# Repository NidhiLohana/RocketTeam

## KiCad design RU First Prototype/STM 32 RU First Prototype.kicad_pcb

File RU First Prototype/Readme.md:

This is the first prototype of RU

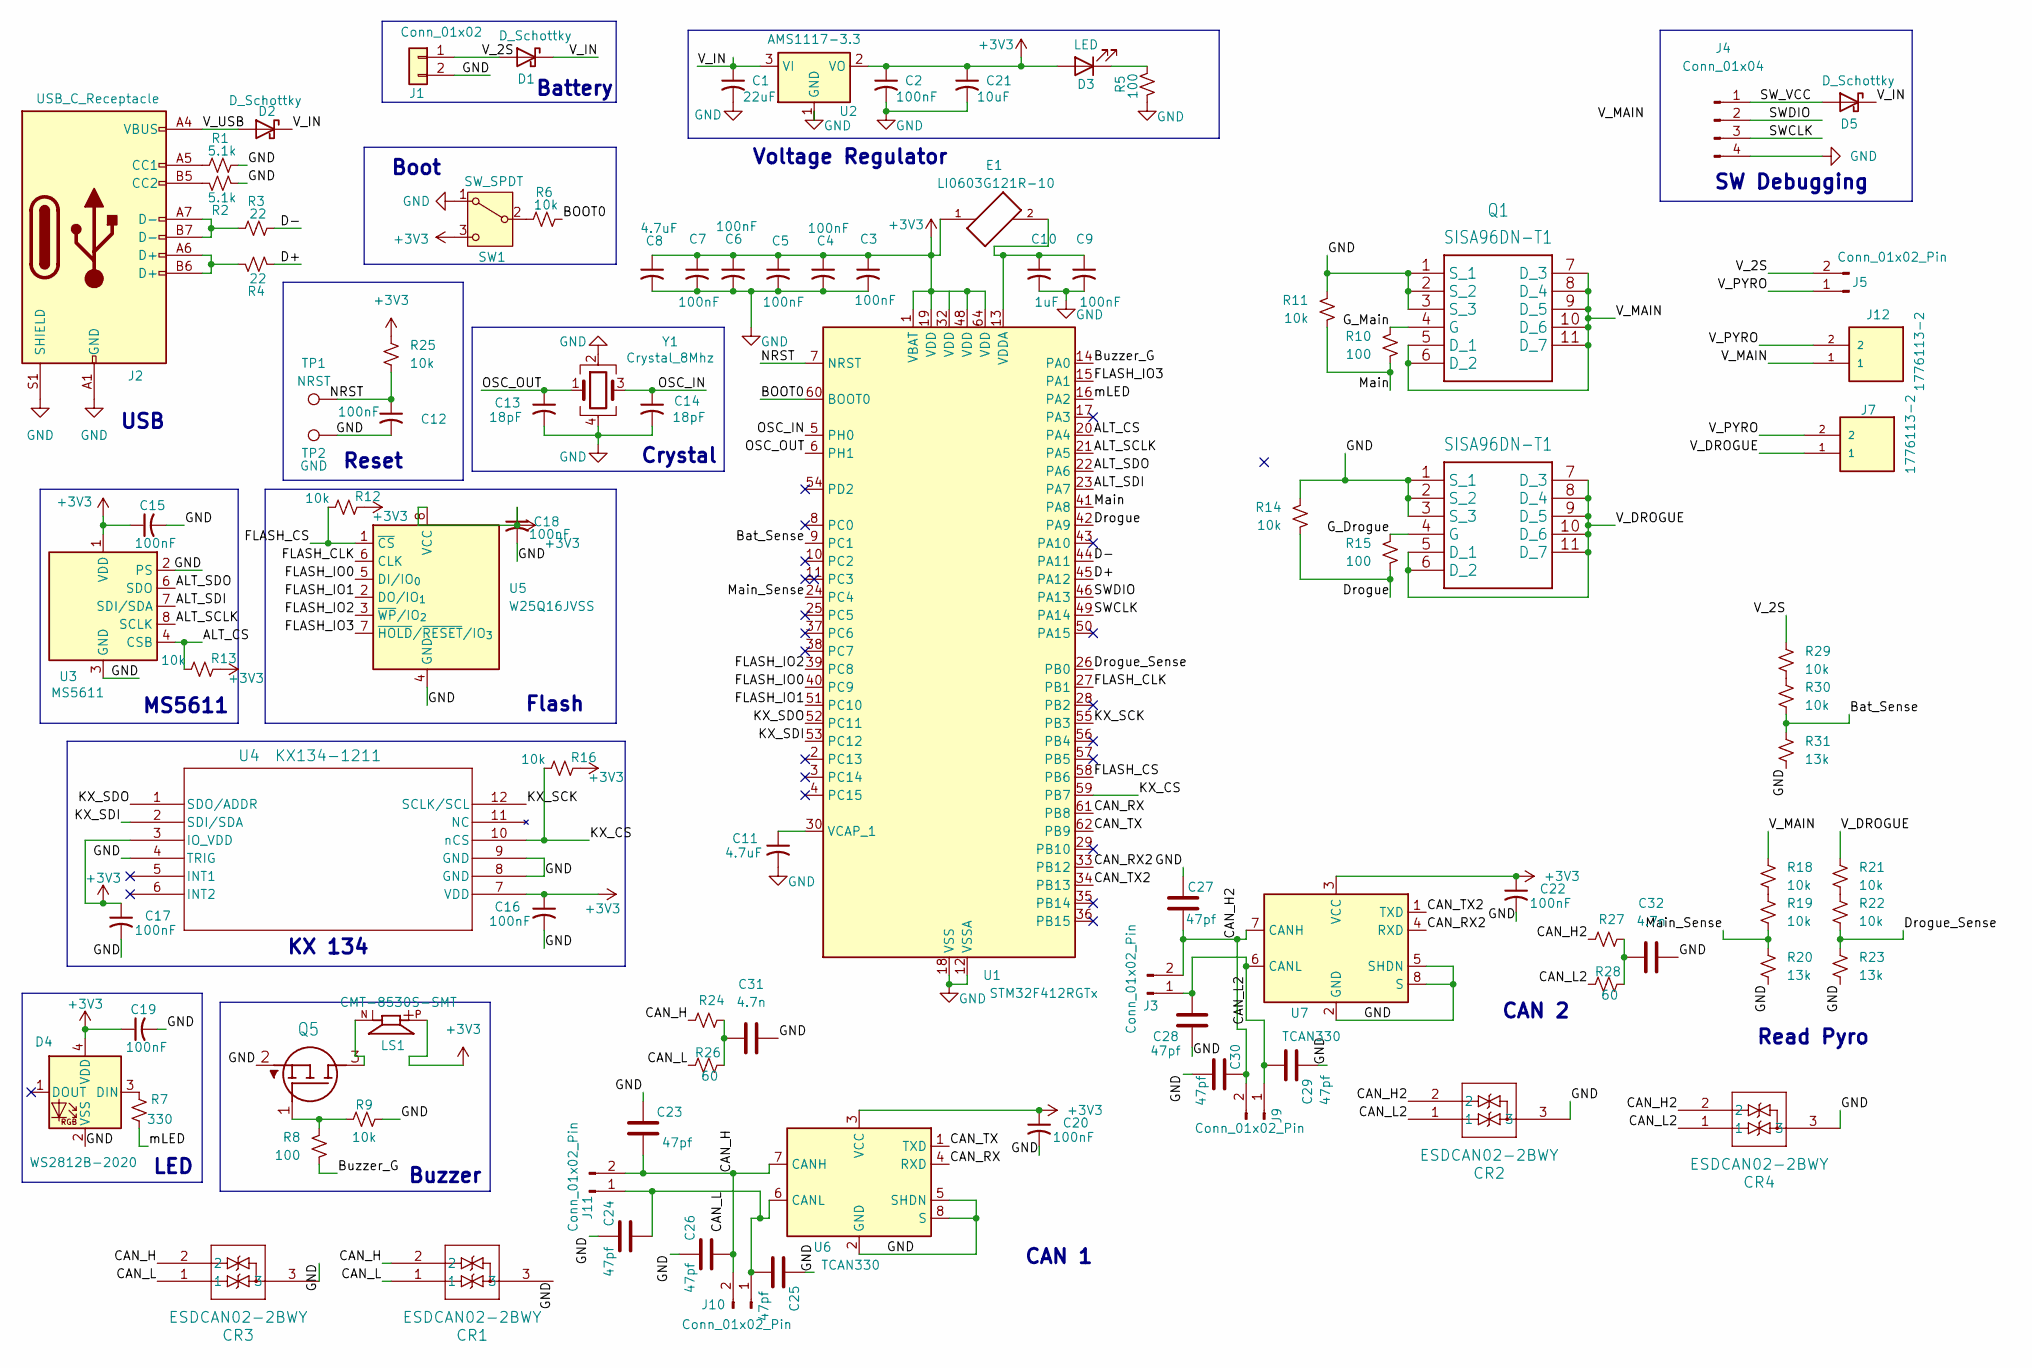
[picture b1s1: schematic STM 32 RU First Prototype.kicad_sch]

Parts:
C1: 22uF; C_0603_1608Metric
C2, C3, C4, C5, C6, C7, C9, C12, C15, C16, C17, C18, C19, C20, C22: 100nF; C_0603_1608Metric
C8, C11: 4.7uF; C_0603_1608Metric
C10: 1uF; C_0603_1608Metric
C13, C14: 18pF; C_0603_1608Metric
C21: 10uF; C_0603_1608Metric
C23, C24, C25, C26, C27, C28, C29, C30: 47pf; C_0603_1608Metric
C31, C32: 4.7n; C_0603_1608Metric
CR1, CR2, CR3, CR4: ESDCAN02-2BWY; SOT323-3L_STM
D1, D2, D5: D_Schottky; D_SOD-128
D3: LED; D_0603_1608Metric
D4: WS2812B-2020; LED_WS2812B-2020_PLCC4_2.0x2.0mm
E1: LI0603G121R-10; FB_LI0603G121R-10; PARTREV C
J1: Conn_01x02; AMASS_XT30U-M_1x02_P5.0mm_Vertical
J2: USB_C_Receptacle; USB_C_Receptacle_GCT_USB4105-xx-A_16P_TopMnt_Horizontal
J3, J9, J10, J11: Conn_01x02_Pin; JST_EH_B2B-EH-A_1x02_P2.50mm_Vertical
J4: Conn_01x04; PinHeader_1x04_P2.54mm_Vertical
J5: Conn_01x02_Pin; AMASS_XT30U-M_1x02_P5.0mm_Vertical
J7, J12: 1776113-2; TE_1776113-2; PART_REV P
LS1: CMT-8530S-SMT; CUI_CMT-8530S-SMT
Q1, Q3: SISA96DN-T1; SIS862DNT1GE3
Q5: SOT95P240X115-3N
R1, R2: 5.1k; R_0603_1608Metric
R3, R4: 22; R_0603_1608Metric
R5, R8, R10, R15: 100; R_0603_1608Metric
R6, R9, R11, R12, R13, R14, R16, R18, R19, R21, R22, R25, R29, R30: 10k; R_0603_1608Metric
R7: 330; R_0603_1608Metric
R20, R23, R31: 13k; R_0603_1608Metric
R24, R26, R27, R28: 60; R_0603_1608Metric
SW1: SW_SPDT; SW_SPDT_PCM12
TP1: NRST; TestPoint_Pad_2.0x2.0mm
TP2: GND; TestPoint_Pad_2.0x2.0mm
U1: STM32F412RGTx; LQFP-64_10x10mm_P0.5mm
U2: AMS1117-3.3; SOT-223-3_TabPin2
U3: MS5611; LGA-8_3x5mm_P1.25mm
U4: KX134-1211; XDCR_KX003-1077
U5: W25Q16JVSS; SOIC-8_5.3x5.3mm_P1.27mm
U6, U7: TCAN330; SOIC-8_3.9x4.9mm_P1.27mm
Y1: Crystal_8Mhz; Crystal_SMD_7050-4Pin_7.0x5.0mm

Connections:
+3V3: C2.1, C3.1, C4.1, C5.1, C6.1, C7.1, C8.1, C15.1, C16.1, C17.1, C18.1, C19.1, C20.1, C21.1, C22.1, D3.2 (A), D4.4 (VDD), E1.1, LS1.P, R12.2, R13.2, R16.2, R25.1, SW1.3 (C), U1.1 (VBAT), U1.19 (VDD), U1.32 (VDD), U1.48 (VDD), U1.64 (VDD), U2.2 (VO), U3.1 (VDD), U4.3 (IO_VDD), U4.7 (VDD), U5.8 (VCC), U6.3 (VCC), U7.3 (VCC)
/ALT_CS: R13.1, U1.20 (PA4), U3.4 (CSB), U3.5 (CSB)
/ALT_SCLK: U1.21 (PA5), U3.8 (SCLK)
/ALT_SDI: U1.23 (PA7), U3.7 (SDI/SDA)
/ALT_SDO: U1.22 (PA6), U3.6 (SDO)
/BOOT0: R6.2, U1.60 (BOOT0)
/Bat_Sense: R30.2, R31.1, U1.9 (PC1)
/Buzzer_G: R8.2, U1.14 (PA0)
/CAN_H: C23.2, C26.2, CR1.2, CR3.2, J10.2, J11.2, R24.1, U6.7 (CANH)
/CAN_H2: C27.2, C30.2, CR2.2, CR4.2, J3.2, J9.2, R27.1, U7.7 (CANH)
/CAN_L: C24.2, C25.2, CR1.1, CR3.1, J10.1, J11.1, R26.1, U6.6 (CANL)
/CAN_L2: C28.2, C29.2, CR2.1, CR4.1, J3.1, J9.1, R28.1, U7.6 (CANL)
/CAN_RX: U1.61 (PB8), U6.4 (RXD)
/CAN_RX2: U1.33 (PB12), U7.4 (RXD)
/CAN_TX: U1.62 (PB9), U6.1 (TXD)
/CAN_TX2: U1.34 (PB13), U7.1 (TXD)
/D+: R4.2, U1.45 (PA12)
/D-: R3.2, U1.44 (PA11)
/Drogue: R14.2, R15.2, U1.42 (PA9)
/Drogue_Sense: R22.2, R23.1, U1.26 (PB0)
/FLASH_CLK: U1.27 (PB1), U5.6 (CLK)
/FLASH_CS: R12.1, U1.58 (PB6), U5.1 (~CS)
/FLASH_IO0: U1.40 (PC9), U5.5 (DI/IO_{0})
/FLASH_IO1: U1.51 (PC10), U5.2 (DO/IO_{1})
/FLASH_IO2: U1.39 (PC8), U5.3 (~WP/IO_{2})
/FLASH_IO3: U1.15 (PA1), U5.7 (~HOLD/~RESET/IO_{3})
/G_Drogue: Q3.4 (G), R15.1
/G_Main: Q1.4 (G), R10.1
/KX_CS: R16.1, U1.59 (PB7), U4.10 (nCS)
/KX_SCK: U1.55 (PB3), U4.12 (SCLK/SCL)
/KX_SDI: U1.53 (PC12), U4.2 (SDI/SDA)
/KX_SDO: U1.52 (PC11), U4.1 (SDO/ADDR)
/Main: R10.2, R11.2, U1.41 (PA8)
/Main_Sense: R19.2, R20.1, U1.24 (PC4)
/NRST: C12.1, R25.2, TP1.1 (1_1), U1.7 (NRST)
/OSC_IN: C14.1, U1.5 (PH0), Y1.3
/OSC_OUT: C13.1, U1.6 (PH1), Y1.1
/SWCLK: J4.3, U1.49 (PA14)
/SWDIO: J4.2, U1.46 (PA13)
/SW_VCC: D5.2 (A), J4.1
/V_2S: D1.2 (A), J1.1, J5.2, R29.1
/V_DROGUE: J7.1, Q3.5 (D_1), Q3.6 (D_2), Q3.7 (D_3), Q3.8 (D_4), Q3.9 (D_5), Q3.10 (D_6), Q3.11 (D_7), R21.1
/V_IN: C1.1, D1.1 (K), D2.1 (K), D5.1 (K), U2.3 (VI)
/V_MAIN: J12.1, Q1.5 (D_1), Q1.6 (D_2), Q1.7 (D_3), Q1.8 (D_4), Q1.9 (D_5), Q1.10 (D_6), Q1.11 (D_7), R18.1
/V_PYRO: J5.1, J7.2, J12.2
/V_USB: D2.2 (A), J2.A4 (VBUS), J2.A9 (VBUS), J2.B4 (VBUS), J2.B9 (VBUS)
/mLED: R7.2, U1.16 (PA2)
GND: C1.2, C2.2, C3.2, C4.2, C5.2, C6.2, C7.2, C8.2, C9.2, C10.2, C11.2, C12.2, C13.2, C14.2, C15.2, C16.2, C17.2, C18.2, C19.2, C20.2, C21.2, C22.2, C23.1, C24.1, C25.1, C26.1, C27.1, C28.1, C29.1, C30.1, C31.2, C32.2, CR1.3, CR2.3, CR3.3, CR4.3, D4.2 (VSS), J1.2, J2.A1 (GND), J2.A12 (GND), J2.B1 (GND), J2.B12 (GND), J2.S1 (SHIELD), J4.4, Q1.1 (S_1), Q1.2 (S_2), Q1.3 (S_3), Q3.1 (S_1), Q3.2 (S_2), Q3.3 (S_3), Q5.2 (S), R1.2, R2.2, R5.2, R9.1, R11.1, R14.1, R20.2, R23.2, R31.2, SW1.1 (A), TP2.1 (1_1), U1.12 (VSSA), U1.18 (VSS), U1.31 (VSS), U1.47 (VSS), U1.63 (VSS), U2.1 (GND), U3.2 (PS), U3.3 (GND), U4.4 (TRIG), U4.8 (GND), U4.9 (GND), U5.4 (GND), U6.2 (GND), U6.5 (SHDN), U6.8 (S), U7.2 (GND), U7.5 (SHDN), U7.8 (S), Y1.2, Y1.4
unnamed: C31.1, R24.2, R26.2
unnamed: C32.1, R27.2, R28.2
unnamed: D3.1 (K), R5.1
unnamed: D4.3 (DIN), R7.1
unnamed: J2.A5 (CC1), R1.1
unnamed: J2.B5 (CC2), R2.1
unnamed: J2.A6 (D+), J2.B6 (D+), R4.1
unnamed: J2.A7 (D-), J2.B7 (D-), R3.1
unnamed: LS1.N, Q5.3 (D)
unnamed: Q5.1 (G), R8.1, R9.2
unnamed: R18.2, R19.1
unnamed: R21.2, R22.1
unnamed: R29.2, R30.1
unnamed: R6.1, SW1.2 (B)
unnamed: C11.1, U1.30 (VCAP_1)
unnamed: C9.1, C10.1, E1.2, U1.13 (VDDA)

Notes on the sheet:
Flash
Voltage Regulator
Buzzer
LED
Battery
Reset
USB
MS5611
CAN 1
Boot
SW Debugging
CAN 2
KX 134
Read Pyro
Crystal

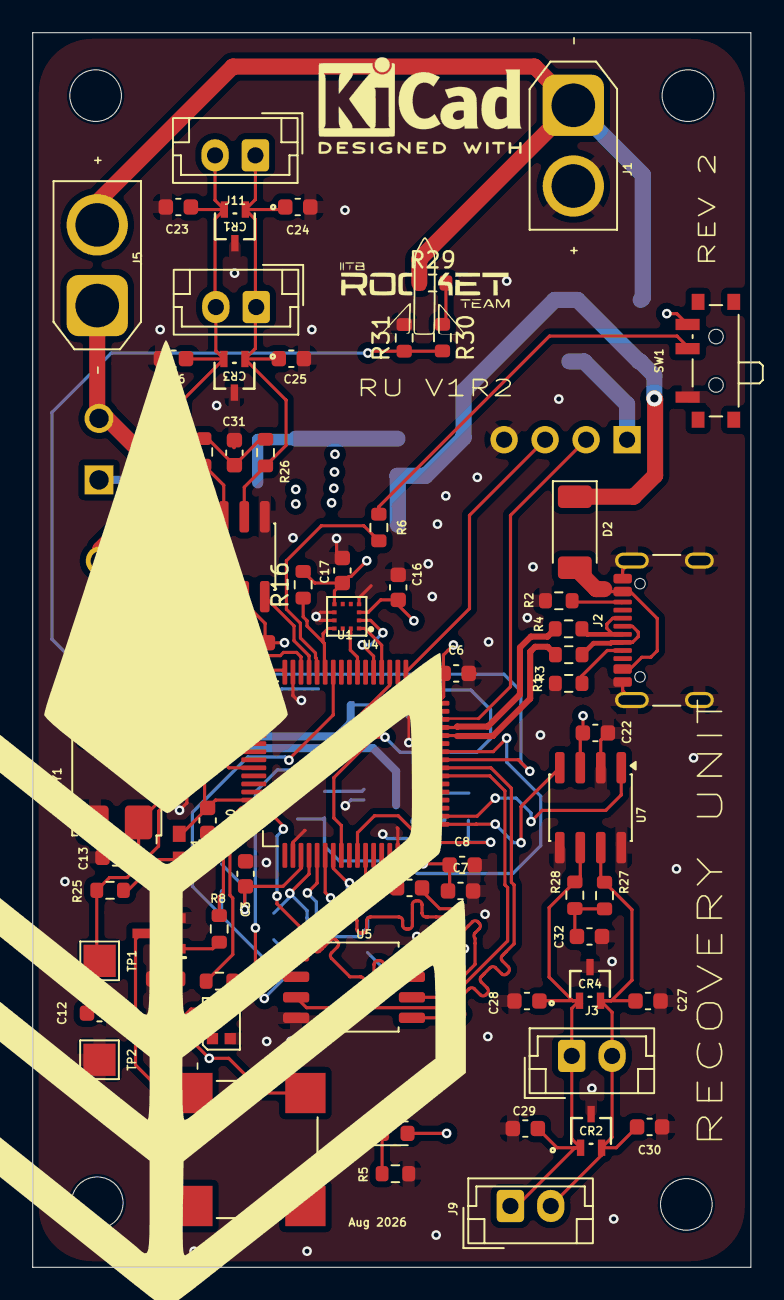
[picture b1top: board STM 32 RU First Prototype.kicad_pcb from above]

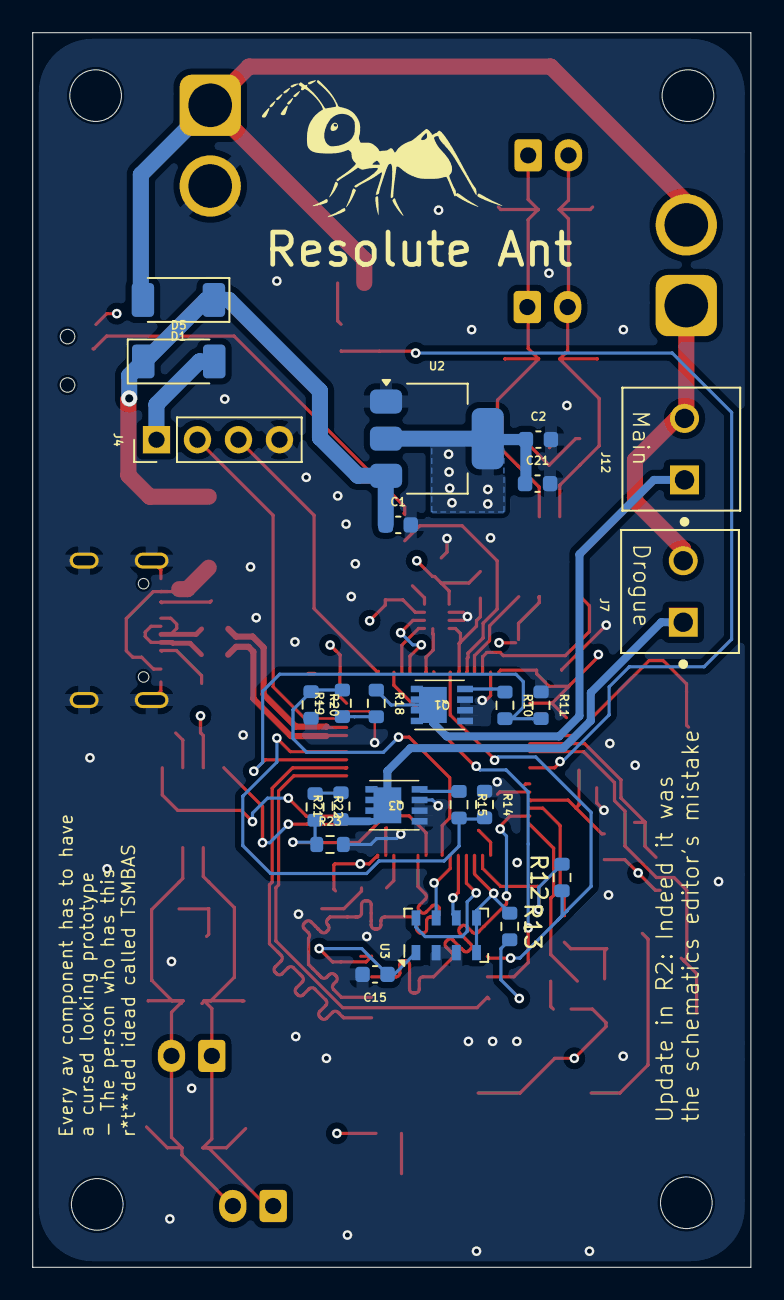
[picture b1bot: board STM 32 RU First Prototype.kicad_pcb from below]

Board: 4 copper layers, 44.5 x 76.5 mm, 97 parts (25 on the bottom side), 64 nets.
